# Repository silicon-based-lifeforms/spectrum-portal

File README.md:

# spectrum portal

## about
Spectrum Portal is a **work-in-progress** open-hardware Eurorack module for interfacing with an oscilloscope, spectrum analyzer, frequency counter, or other device of interest. 

## features
- Connect up to two Eurorack signals to two dedicated SMA outputs (and then hook up to your scope with a BNC-SMA adapter)
- Keep a copy of your signals using a built-in buffered multiple, one for each of the two inputs.
- A whole butt ton of circuit protection mechanisms with many pairs of belts and suspenders.

## motivations
- Seeing and studying the waveforms you're creating is a fantastic tool for exploring synthesis. It's a really exciting thing to see, and it really enhances my modular experience. 
- Modules with a built in Oscilloscope are pretty cool. But I already have a dedicated Oscilloscope that would fit the bit really nicely, plus I'd love to be able to hookup a modular to an analog CRT scope for the coolness factor.
- I'm fascinated by oscilloscope art and am excited by the possibilities of creating oscilloscope art with a modular synth.
- I wanted something more robust than a passive adapter/cable, that lived inside the rack as a dedicated module. 
- I just want to design and build eurorack modules.
- I want to further the proliferation of open-hardware eurorack modules across the galaxy

## design goals
- Open-hardware
- Must be fully user-servicable and user-buildable (big SMD components that are easy to hand-solder are fine, tiny packages that require specialized equipment is not fine)
- Strike a good compromise between features, quality, size and cost. Quality comes at the expense of added cost, features come at the expense of added size (and added cost).

## contributing
Contributions are heavily encouraged! There are many areas where the design can be significantly improved (it's still a work-in-progress, afterall).

## licensing
- The hardware is licensed under the strongly reciprocal variant of the [CERN Open Hardware License](https://ohwr.org/project/cernohl/wikis/Documents/CERN-OHL-version-2) (specifically CERN-OHL-S).
- There's no source code for this module, it's a pure hardware affair. But any future modules that have firmware will have that firmware licensed under the GNU GPL v3.
- There's no documentation (yet), but any future documentation will be licensed under an appropriate open-source license.

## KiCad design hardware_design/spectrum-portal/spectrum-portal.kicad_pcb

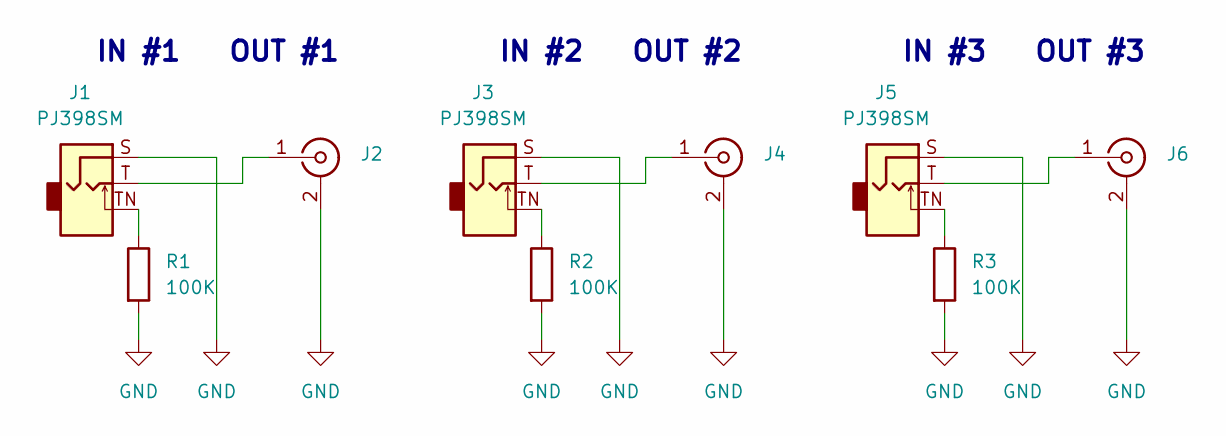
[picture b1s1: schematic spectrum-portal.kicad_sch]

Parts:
J1, J3, J5: PJ398SM; Jack_3.5mm_QingPu_WQP-PJ398SM_Vertical
J2, J4, J6: CONN_132291_AMP; DIGIKEY_PART ACX1976-ND
R1, R2, R3: 100K; R_1206_3216Metric_Pad1.30x1.75mm_HandSolder

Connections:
GND: J1.S, J2.2 (Ext), J3.S, J4.2 (Ext), J5.S, J6.2 (Ext), R1.2, R2.2, R3.2
unnamed: J1.TN, R1.1
unnamed: J1.T, J2.1 (In)
unnamed: J3.TN, R2.1
unnamed: J3.T, J4.1 (In)
unnamed: J5.TN, R3.1
unnamed: J5.T, J6.1 (In)

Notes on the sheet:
IN #3
OUT #1
IN #2
OUT #3
OUT #2
IN #1

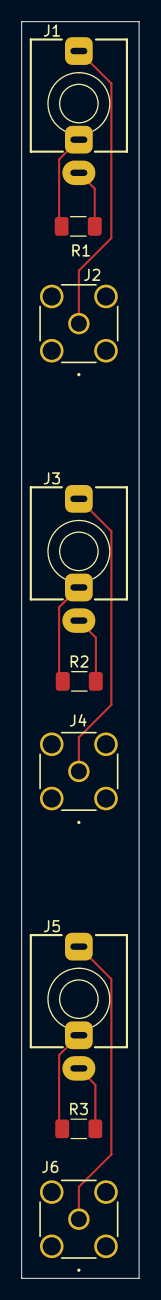
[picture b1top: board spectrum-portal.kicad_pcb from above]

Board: 2 copper layers, 11.0 x 117.7 mm, 9 parts (0 on the bottom side), 7 nets.

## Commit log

2024-04-08 WIP 4HP design
2024-04-09 Redesigned as 5HP, added protection components
2024-04-09 Switch to more affordable SMA connector
2024-04-09 Add render of PCB for README file
2024-04-09 Update bill of materials, add .pdf of schematic
2024-04-09 Create LICENSE
2024-04-10 Fix SMA connector
2024-04-10 Add exclusions for silkscreen over copper violations
2024-04-10 Redesigned as passive module in 3HP
